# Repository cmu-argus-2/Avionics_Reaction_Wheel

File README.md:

Equipment:
- DC Power Supply (set to 12V, 0.9A) 
- Nucleo-G474RE mircocontroller board
- MCF8315C motor driver (on MCF8315EVM board, use VBAT not VM)
- 2804 Three Phase Brushless Motor / AS5600 FOC Encoder (DFRobot, SKU: FIT1034)

Arduino IDE Setup:
- Need STM32 MCU based boards by STMircoelectronics board manager installed
- Select Tools > Board part number: > Nucleo G474RE
- Select Nucleo-64 from board & port menu

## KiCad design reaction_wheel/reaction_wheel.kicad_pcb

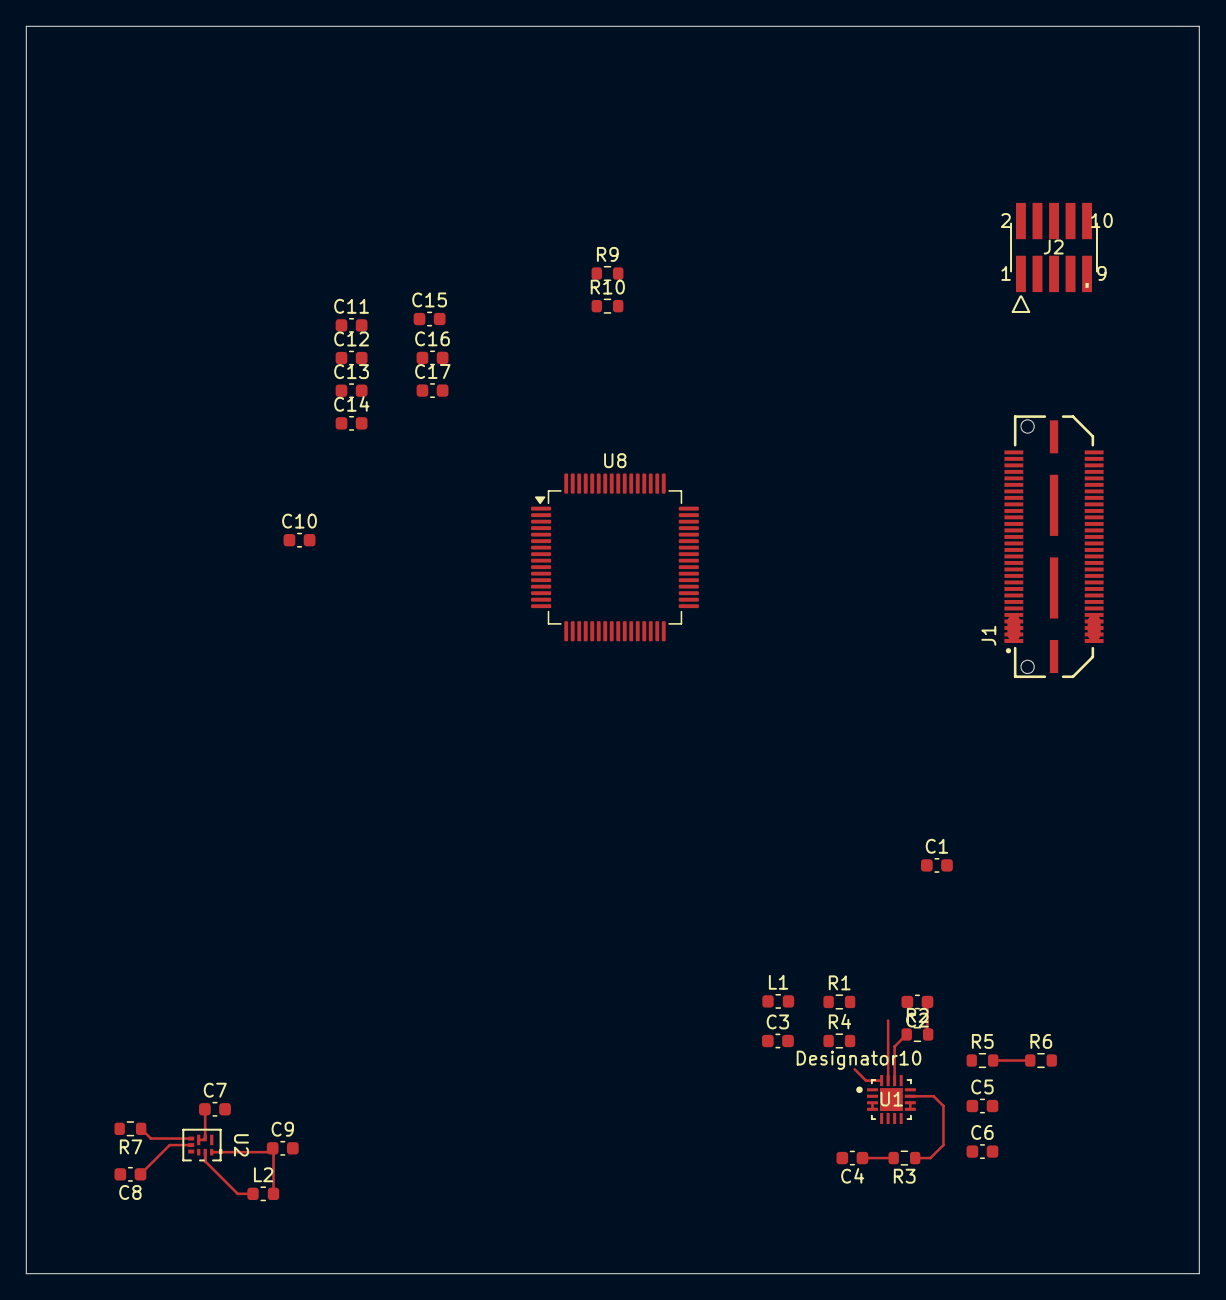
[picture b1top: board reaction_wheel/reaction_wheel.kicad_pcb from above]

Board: 2 copper layers, 90.2 x 95.9 mm, 33 parts (0 on the bottom side), 32 nets.

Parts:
C1, C6, C9: 22uF; C_0603_1608Metric
C2: 4.7nF; C_0603_1608Metric
C3: 0.1uF; C_0603_1608Metric
C4: 2.2uF; C_0603_1608Metric
C5: 1uF; C_0603_1608Metric
C7: 10uF; C_0603_1608Metric
C8: 10nF; C_0603_1608Metric
C10, C11, C12, C13, C14, C15, C16, C17: 100nF; C_0603_1608Metric
J1: QTH-030-01-L-D-A; SAMTEC-QTH-030-01-X-D-A
J2: FTSH-105-01-L-DV; CON10_2X5_DU_FTSH_SAI
L1, L2: 1uH; L_0603_1608Metric
R1, R3: 100k; R_0603_1608Metric
R2: 10k; R_0603_1608Metric
R4: 18k; R_0603_1608Metric
R5: 280k; R_0603_1608Metric
R6: 20k; R_0603_1608Metric
R7: 26.1k; R_0603_1608Metric
R9, R10: 4.7k; R_0603_1608Metric
U1: TPS61379QWRTERQ1; RTE0016K-IPC_B
U2: TPS62902RPJR; QFN_902RPJR_TEX
U8: STM32G474RETx; LQFP-64_10x10mm_P0.5mm

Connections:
+3V3: C9.1, C11.1, C12.1, C13.1, C14.1, C15.1, C16.1, C17.1, J2.1, L2.2, R9.1, R10.1, U2.3 (VOS), U8.1 (VBAT), U8.16 (VDD), U8.28 (VREF+), U8.29 (VDDA), U8.32 (VDD), U8.48 (VDD), U8.64 (VDD)
+3V3_P: J1.21, J1.22, J1.23, J1.24
/ADCS_EN: J1.38, U8.42 (PA8)
/NRST: C10.1, J2.10, U8.7 (PG10)
/Power/+12V: C5.1, C6.1, R5.1, U1.9 (VO), U1.10 (OUT)
/Power/BST_Boost: C3.2, U1.2 (BST)
/Power/COMP_Boost: R2.1, U1.14 (COMP)
/Power/EN_Boost: R1.2, U1.15 (EN)
/Power/FB_Boost: R5.2, R6.1, U1.13 (FB)
/Power/FREQ_Boost: R4.1, U1.16 (FREQ)
/Power/MODE_SCONF_Buck: R7.1, U2.7 (MODE/S-CONF)
/Power/PG_Boost: R3.1, U1.11 (PG)
/Power/SS_TR_Buck: C8.1, U2.8 (SS/TR)
/Power/SW_Boost: C3.1, L1.2, U1.3 (SW), U1.4 (SW)
/Power/SW_Buck: L2.1, U2.2 (SW)
/Power/VCC_Boost: C4.1, R3.2, U1.6 (VCC)
/RW_EN: J1.47, U8.17 (PA3)
/RW_MTR_ALRM: J1.53, U8.14 (PA2)
/RW_MTR_FLT: J1.51, U8.12 (PA0)
/RW_PWR_FLT: J1.49, U8.13 (PA1)
/RW_SCL: J1.55, R9.2, U8.59 (PB6)
/RW_SDA: J1.57, R10.2, U8.60 (PB7)
/SPIO_CLK: J1.29, U8.19 (PA5)
/SPIO_MISO: J1.33, U8.20 (PA6)
/SPIO_MOSI: J1.31, U8.21 (PA7)
/SPIO_NSS: J1.36, U8.18 (PA4)
/SWDCLK: J2.4, U8.50 (PA14)
/SWDIO: J2.2, U8.49 (PA13)
/SWO: J2.6, U8.56 (PB3)
GND: C1.2, C2.2, C4.2, C5.2, C6.2, C7.2, C8.2, C9.2, C10.2, C11.2, C12.2, C13.2, C14.2, C15.2, C16.2, C17.2, J1.11, J1.12, J1.13, J1.14, J1.15, J1.16, J1.17, J1.18, J1.19, J1.20, J1.25, J1.26, J1.27, J1.28, J1.35, J1.41, J1.44, J1.45, J1.59, J1.60, J2.3, J2.5, J2.9, R4.2, R6.2, R7.2, U1.5 (MODE_SYNC), U1.7 (GND), U1.8 (GND), U1.17 (Thermal_Pad), U2.4 (GND), U8.15 (VSS), U8.27 (VSSA), U8.31 (VSS), U8.47 (VSS), U8.63 (VSS)
unnamed: C2.1, R2.2
VBATT: C1.1, C7.1, J1.01 (Pin_1), J1.02 (Pin_2), J1.03 (Pin_3), J1.04 (Pin_4), J1.05 (Pin_5), J1.06 (Pin_6), J1.07 (Pin_7), J1.08 (Pin_8), J1.09 (Pin_9), J1.10, L1.1, R1.1, U1.1 (VIN), U2.5 (EN), U2.6 (VIN)

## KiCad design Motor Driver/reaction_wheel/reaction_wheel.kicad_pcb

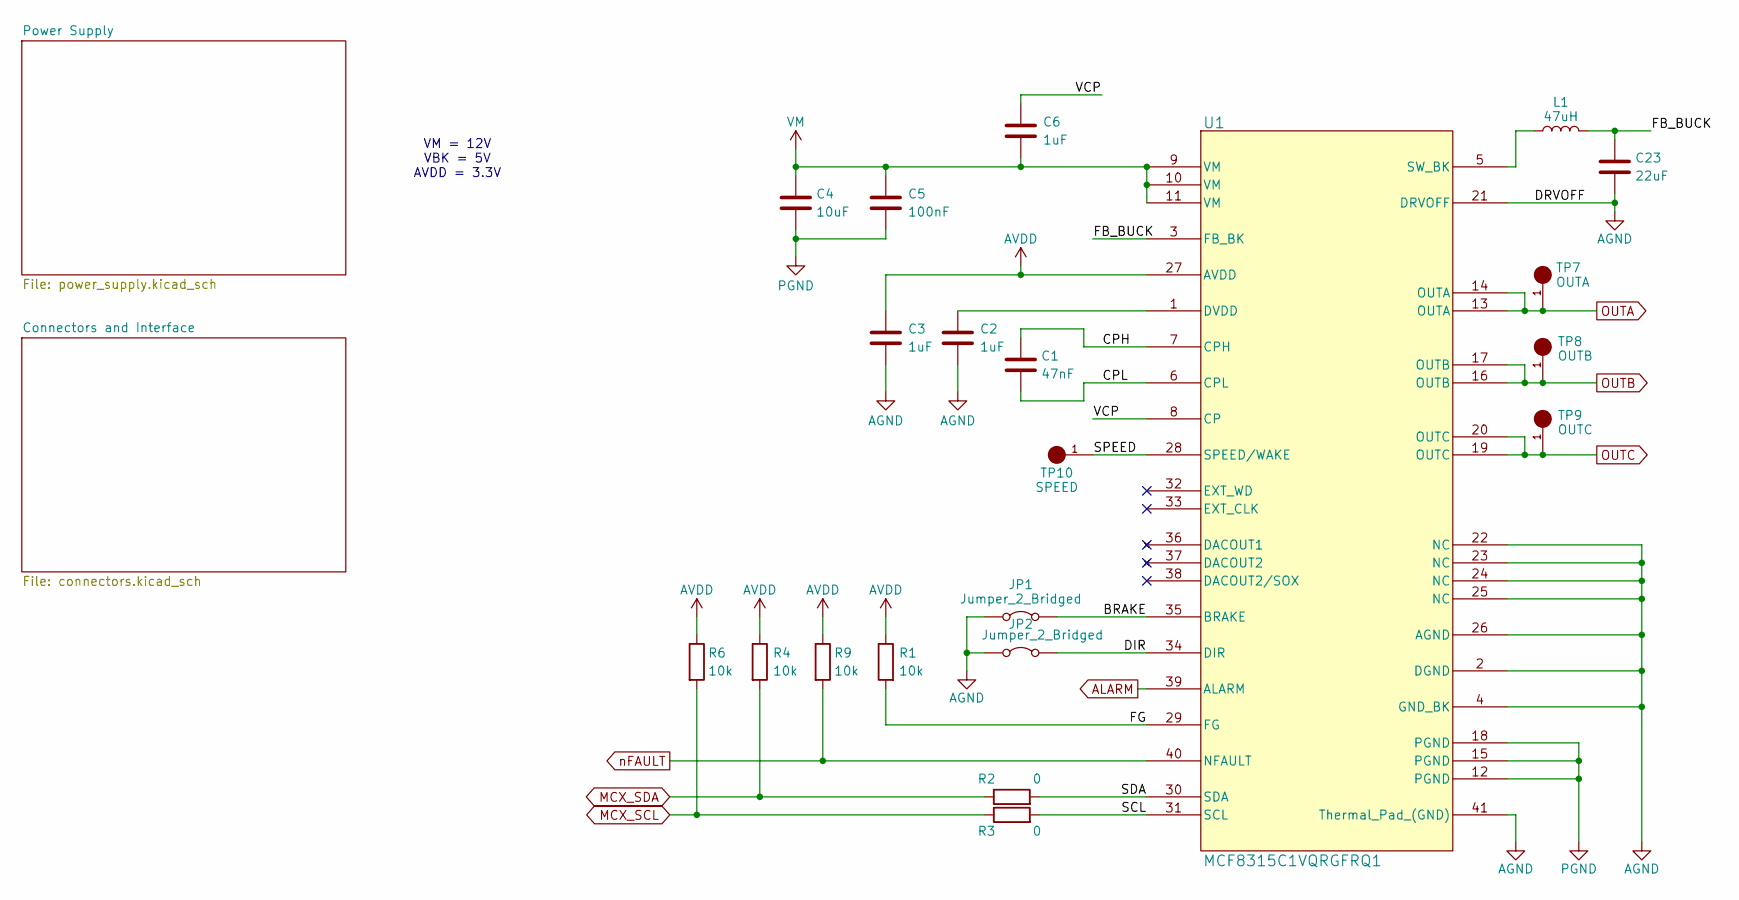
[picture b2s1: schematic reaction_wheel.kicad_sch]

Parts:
C1: 47nF; C_0603_1608Metric
C2, C3, C6: 1uF; C_0603_1608Metric
C4: 10uF; C_0805_2012Metric
C5: 100nF; C_0603_1608Metric
C23: 22uF; C_0603_1608Metric
JP1, JP2: Jumper_2_Bridged; SolderJumper-2_P1.3mm_Bridged_RoundedPad1.0x1.5mm
L1: 47uH; L_0603_1608Metric
R1, R4, R6, R9: 10k; R_0603_1608Metric
R2, R3: 0; R_0603_1608Metric
TP7: OUTA; TestPoint_Keystone_5000-5004_Miniature; MPN 5001; Digikey PN 36-5001-ND
TP8: OUTB; TestPoint_Keystone_5000-5004_Miniature; MPN 5001; Digikey PN 36-5001-ND
TP9: OUTC; TestPoint_Keystone_5000-5004_Miniature; MPN 5001; Digikey PN 36-5001-ND
TP10: SPEED; TestPoint_Keystone_5000-5004_Miniature; MPN 5001; Digikey PN 36-5001-ND
U1: MCF8315C1VQRGFRQ1; MCF8315C; MPN MCF8315C1VQRGFRQ1; Digikey PN 296-MCF8315C1VQRGFRQ1CT-ND

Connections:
/BRAKE: JP1.2 (B), U1.35 (BRAKE)
/CPH: C1.1, U1.7 (CPH)
/CPL: C1.2, U1.6 (CPL)
/DIR: JP2.2 (B), U1.34 (DIR)
/FB_BUCK: C23.1, L1.2, U1.3 (FB_BK)
/FG: R1.2, U1.29 (FG)
/SCL: R3.2, U1.31 (SCL)
/SDA: R2.2, U1.30 (SDA)
/SPEED: TP10.1, U1.28 (SPEED/WAKE)
/VCP: C6.1, U1.8 (CP)
AGND: C2.2, C3.2, C23.2, JP1.1 (A), JP2.1 (A), U1.2 (DGND), U1.4 (GND_BK), U1.21 (DRVOFF), U1.22 (NC), U1.23 (NC), U1.24 (NC), U1.25 (NC), U1.26 (AGND), U1.41 (Thermal_Pad_(GND)); also elsewhere on the board
ALARM: U1.39 (ALARM); also elsewhere on the board
AVDD: C3.1, R1.1, R4.1, R6.1, R9.1, U1.27 (AVDD)
MCX_SCL: R3.1, R6.2; also elsewhere on the board
MCX_SDA: R2.1, R4.2; also elsewhere on the board
unnamed: C2.1, U1.1 (DVDD)
unnamed: L1.1, U1.5 (SW_BK)
OUTA: TP7.1, U1.13 (OUTA), U1.14 (OUTA); also elsewhere on the board
OUTB: TP8.1, U1.16 (OUTB), U1.17 (OUTB); also elsewhere on the board
OUTC: TP9.1, U1.19 (OUTC), U1.20 (OUTC); also elsewhere on the board
PGND: C4.2, C5.2, U1.12 (PGND), U1.15 (PGND), U1.18 (PGND); also elsewhere on the board
VM: C4.1, C5.1, C6.2, U1.9 (VM), U1.10 (VM), U1.11 (VM); also elsewhere on the board
nFAULT: R9.2, U1.40 (NFAULT); also elsewhere on the board

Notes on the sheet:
VM = 12V VBK = 5V AVDD = 3.3V

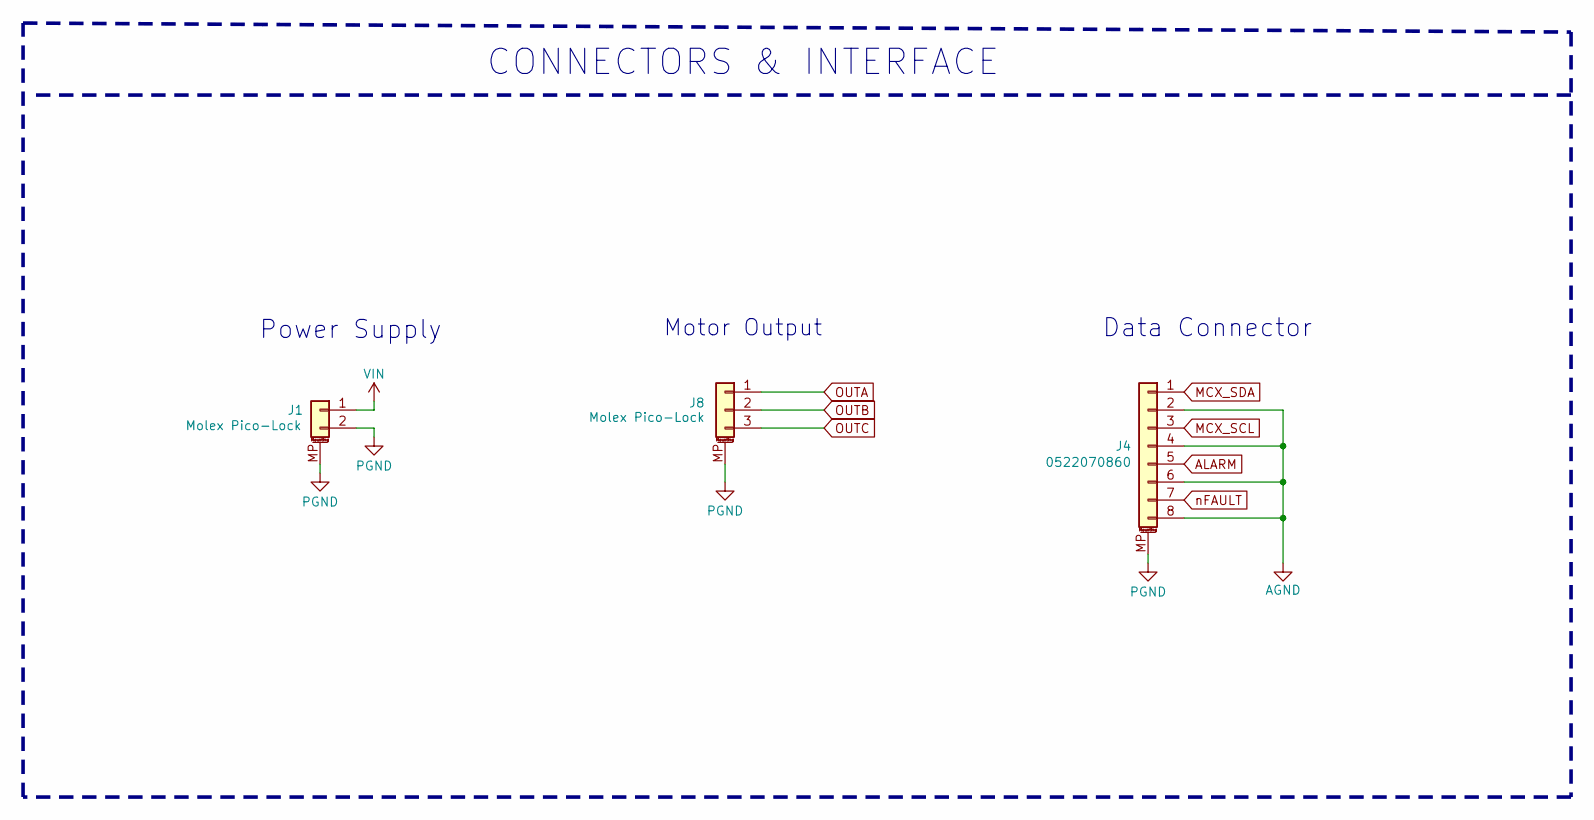
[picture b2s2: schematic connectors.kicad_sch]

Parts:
J1: Molex Pico-Lock; Molex_Pico-Lock_504050-0291_1x02-1MP_P1.50mm_Horizontal; Part Num 0781710002
J4: 0522070860; Molex 1x8 Right-Angle Conn; DigiKey PN 0522070860
J8: Molex Pico-Lock; Molex Pico-Lock 3 Socket Header; Part Number 0781710003

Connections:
AGND: J4.2, J4.4, J4.6, J4.8; also elsewhere on the board
ALARM: J4.5; also elsewhere on the board
MCX_SCL: J4.3; also elsewhere on the board
MCX_SDA: J4.1; also elsewhere on the board
OUTA: J8.1; also elsewhere on the board
OUTB: J8.2; also elsewhere on the board
OUTC: J8.3; also elsewhere on the board
PGND: J1.2, J1.MP (MountPin), J4.MP (MountPin), J8.MP (MountPin); also elsewhere on the board
VIN: J1.1; also elsewhere on the board
nFAULT: J4.7; also elsewhere on the board

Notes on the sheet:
CONNECTORS & INTERFACE
Data Connector
Motor Output
Power Supply

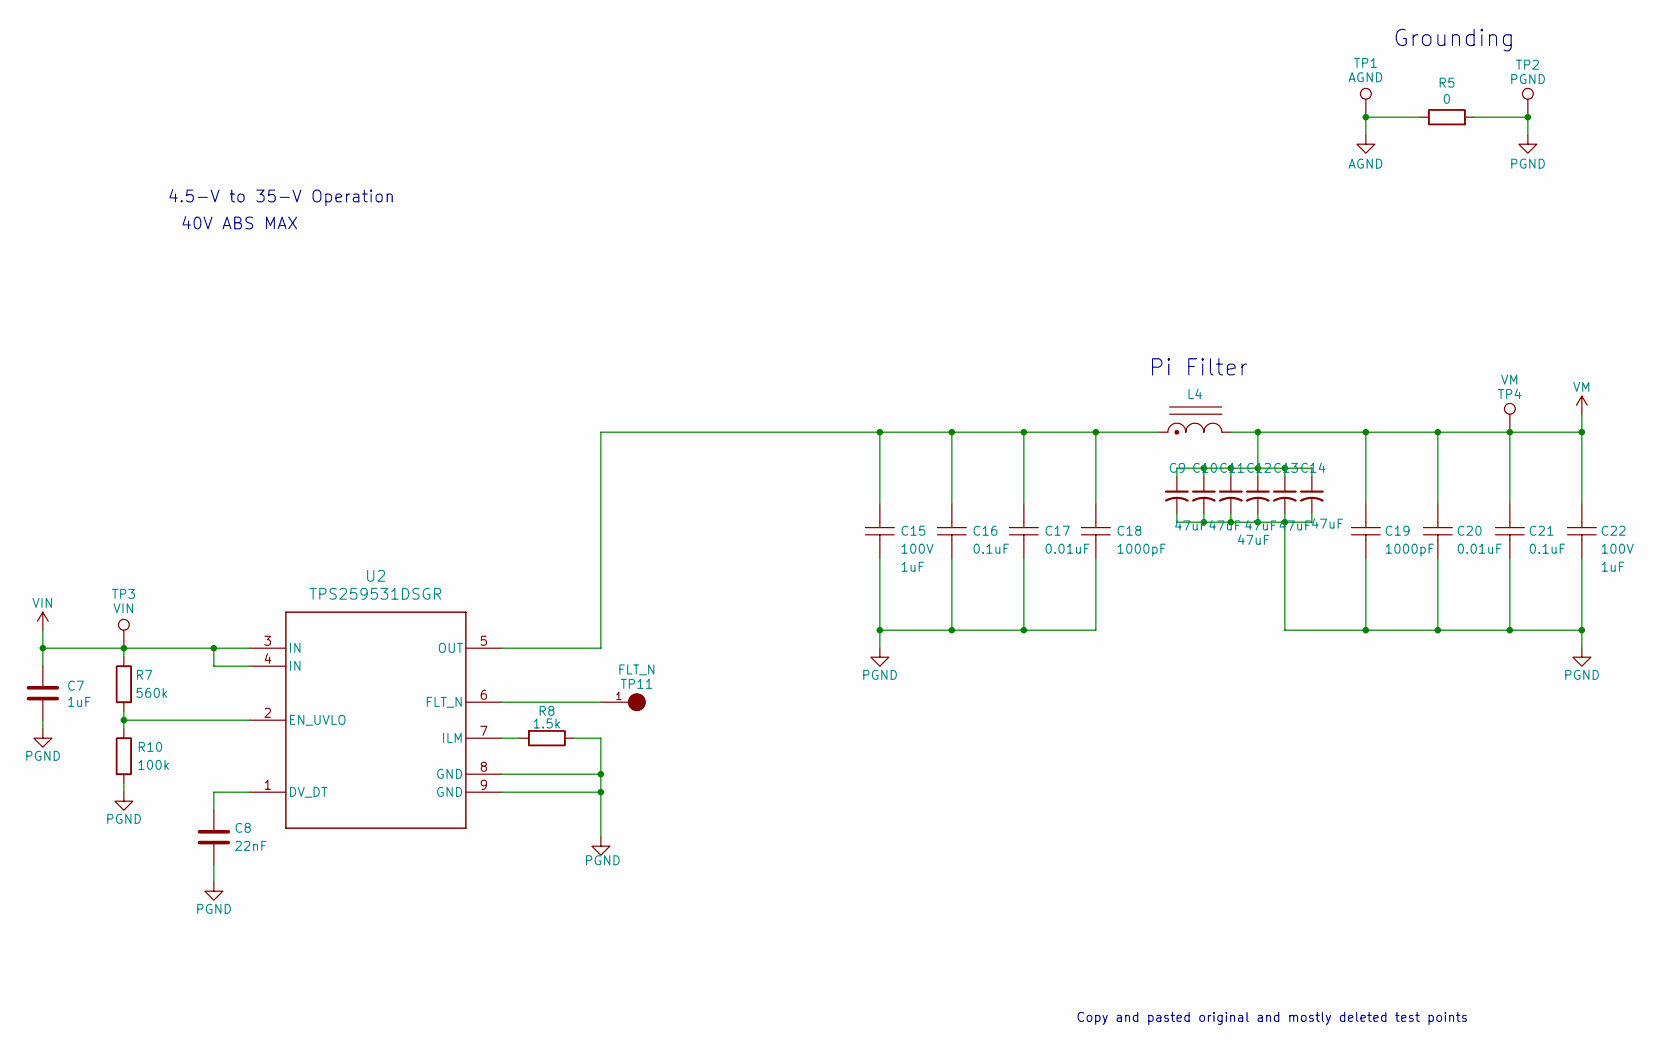
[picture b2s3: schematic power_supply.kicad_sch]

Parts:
C7: 1uF; C_0603_1608Metric
C8: 22nF; C_0603_1608Metric
C9, C10, C11, C12, C13, C14: 47uF; C_1206_3216Metric; DigiKey PN C3216X5R1E476M160AC
C15, C22: CGA3E3X7S2A104K080AB; C_0603_1608Metric; TOLERANCE_% 10%; PARTNUMBER CL31B105KCHNNNE
C16, C21: CGA3E3X7S2A104K080AB; C_0603_1608Metric; TOLERANCE_% 10%; PARTNUMBER CGA3E3X7S2A104K080AB
C17, C20: CGA3E2X7R2A103K080AA; C_0603_1608Metric; TOLERANCE_% 10%; PARTNUMBER CGA3E2X7R2A103K080AA
C18, C19: CGA3E2X7R2A102K080AA; C_0603_1608Metric; TOLERANCE_% 10%; PARTNUMBER CGA3E2X7R2A102K080AA
L4: XAL5030-102MEC; L_Coilcraft_XAL5030-XXX
R5: 0; R_0603_1608Metric
R7: 560k; R_0603_1608Metric
R8: 1.5k; R_0603_1608Metric
R10: 100k; R_0603_1608Metric
TP1: AGND; TestPoint_Keystone_5000-5004_Miniature
TP2: PGND; TestPoint_Keystone_5000-5004_Miniature
TP3: VIN; TestPoint_Keystone_5000-5004_Miniature
TP4: VM; TestPoint_Keystone_5000-5004_Miniature
TP11: FLT_N; TestPoint_Keystone_5000-5004_Miniature; MPN 5001; Digikey PN 36-5001-ND
U2: TPS259531DSGR; eFuse TPS259531DSGR_NV; Part Number TPS259531DSGR

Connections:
AGND: R5.1, TP1.1 (1_1); also elsewhere on the board
unnamed: C8.1, U2.1 (DV_DT)
unnamed: R7.2, R10.1, U2.2 (EN_UVLO)
unnamed: TP11.1, U2.6 (FLT_N)
unnamed: R8.2, U2.7 (ILM)
unnamed: C15.1, C16.1, C17.1, C18.1, L4.1, U2.5 (OUT)
PGND: C7.2, C8.2, C9.2, C10.2, C11.2, C12.2, C13.2, C14.2, C15.2, C16.2, C17.2, C18.2, C19.2, C20.2, C21.2, C22.2, R5.2, R8.1, R10.2, TP2.1 (1_1), U2.8 (GND), U2.9 (GND); also elsewhere on the board
VIN: C7.1, R7.1, TP3.1 (1_1), U2.3 (IN), U2.4 (IN); also elsewhere on the board
VM: C9.1, C10.1, C11.1, C12.1, C13.1, C14.1, C19.1, C20.1, C21.1, C22.1, L4.2, TP4.1 (1_1); also elsewhere on the board

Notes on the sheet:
40V ABS MAX
Grounding
Copy and pasted original and mostly deleted test points
Pi Filter
4.5-V to 35-V Operation

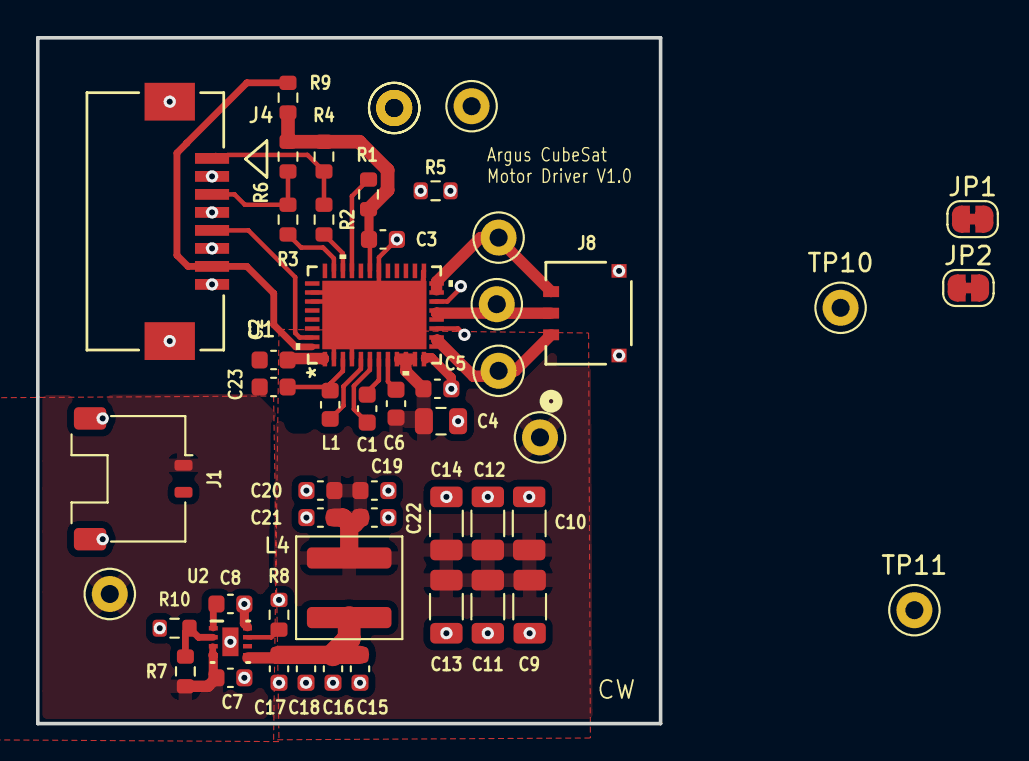
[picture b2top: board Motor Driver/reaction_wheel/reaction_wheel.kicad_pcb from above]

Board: 2 copper layers, 34.6 x 38.1 mm, 52 parts (0 on the bottom side), 29 nets.

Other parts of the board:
TP1#2: AGND; TestPoint_Keystone_5000-5004_Miniature

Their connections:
AGND: TP1#2.1 (1_1); also elsewhere on the board

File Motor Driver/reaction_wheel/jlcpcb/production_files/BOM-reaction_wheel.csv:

Comment,Designator,Footprint,LCSC,Quantity
0,"R2,R3,R5",R_0603_1608Metric,C1952,3
100k,R10,R_0603_1608Metric,C15458,1
100nF,C5,C_0603_1608Metric,C1591,1
10k,"R4,R6",R_0603_1608Metric,C15401,2
10uF,C4,C_0805_2012Metric,C15850,1
1500,R8,R_0603_1608Metric,C22843,1
1uF,"C2,C3,C6,C7",C_0603_1608Metric,C15849,4
22nF,C8,C_0603_1608Metric,C21122,1
22uF,C23,C_0603_1608Metric,C86295,1
47nF,C1,C_0603_1608Metric,C1622,1
47uH,L1,L_0603_1608Metric,C3910945,1
5.1k,"R1,R9",R_0603_1608Metric,C23186,2
560k,R7,R_0603_1608Metric,C23203,1
CGA3E2X7R2A102K080AA,"C18,C19",C_0603_1608Metric,C1588,2
CGA3E2X7R2A103K080AA,"C17,C20",C_0603_1608Metric,C1589,2
CGA3E3X7S2A104K080AB,"C15,C22",C_0603_1608Metric,C15849,2
CGA3E3X7S2A104K080AB,"C16,C21",C_0603_1608Metric,C1591,2
Data Conn,J4,Molex 1x8 Right-Angle Conn,C587867,1
Input Power,J1,Molex_Pico-Lock_504050-0291_1x02-1MP_P1.50mm_Horizontal,C5119943,1
MCF8315C1VQRGFRQ1,U1,MCF8315C,C31301704,1
MOTOR_OUT,J8,Molex Pico-Lock 3 Socket Header,C564183,1
TPS259531DSGR,U2,eFuse TPS259531DSGR_NV,C2155674,1
XAL5030-102MEC,L4,L_Coilcraft_XAL5030-XXX,C5379798,1

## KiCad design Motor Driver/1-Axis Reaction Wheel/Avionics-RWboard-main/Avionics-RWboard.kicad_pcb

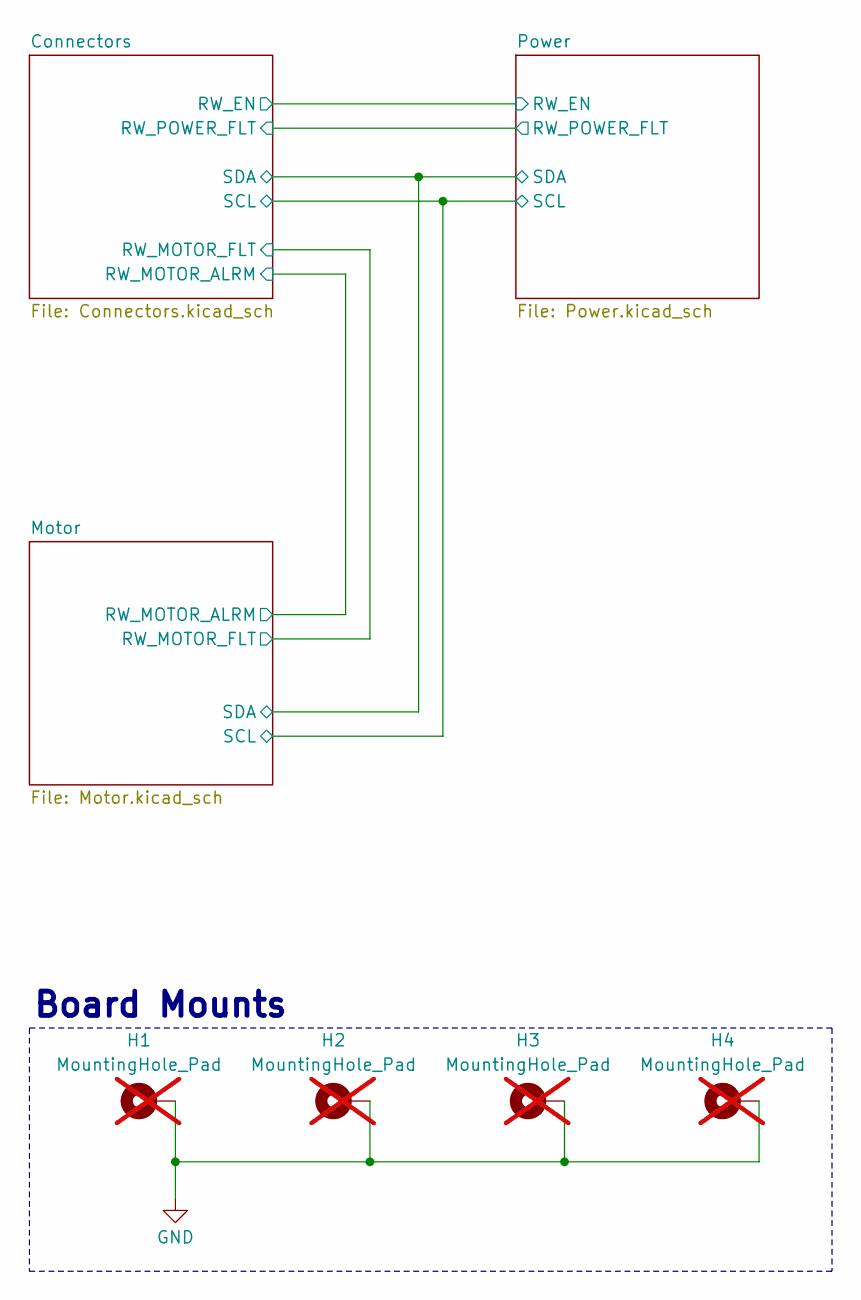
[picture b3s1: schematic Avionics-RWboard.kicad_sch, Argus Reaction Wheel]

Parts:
H1, H2, H3, H4: MountingHole_Pad; MountingHole_3.2mm_M3_Pad_Via; not fitted

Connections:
GND: H1.1 (1_1), H2.1 (1_1), H3.1 (1_1), H4.1 (1_1); also elsewhere on the board

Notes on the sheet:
Board Mounts

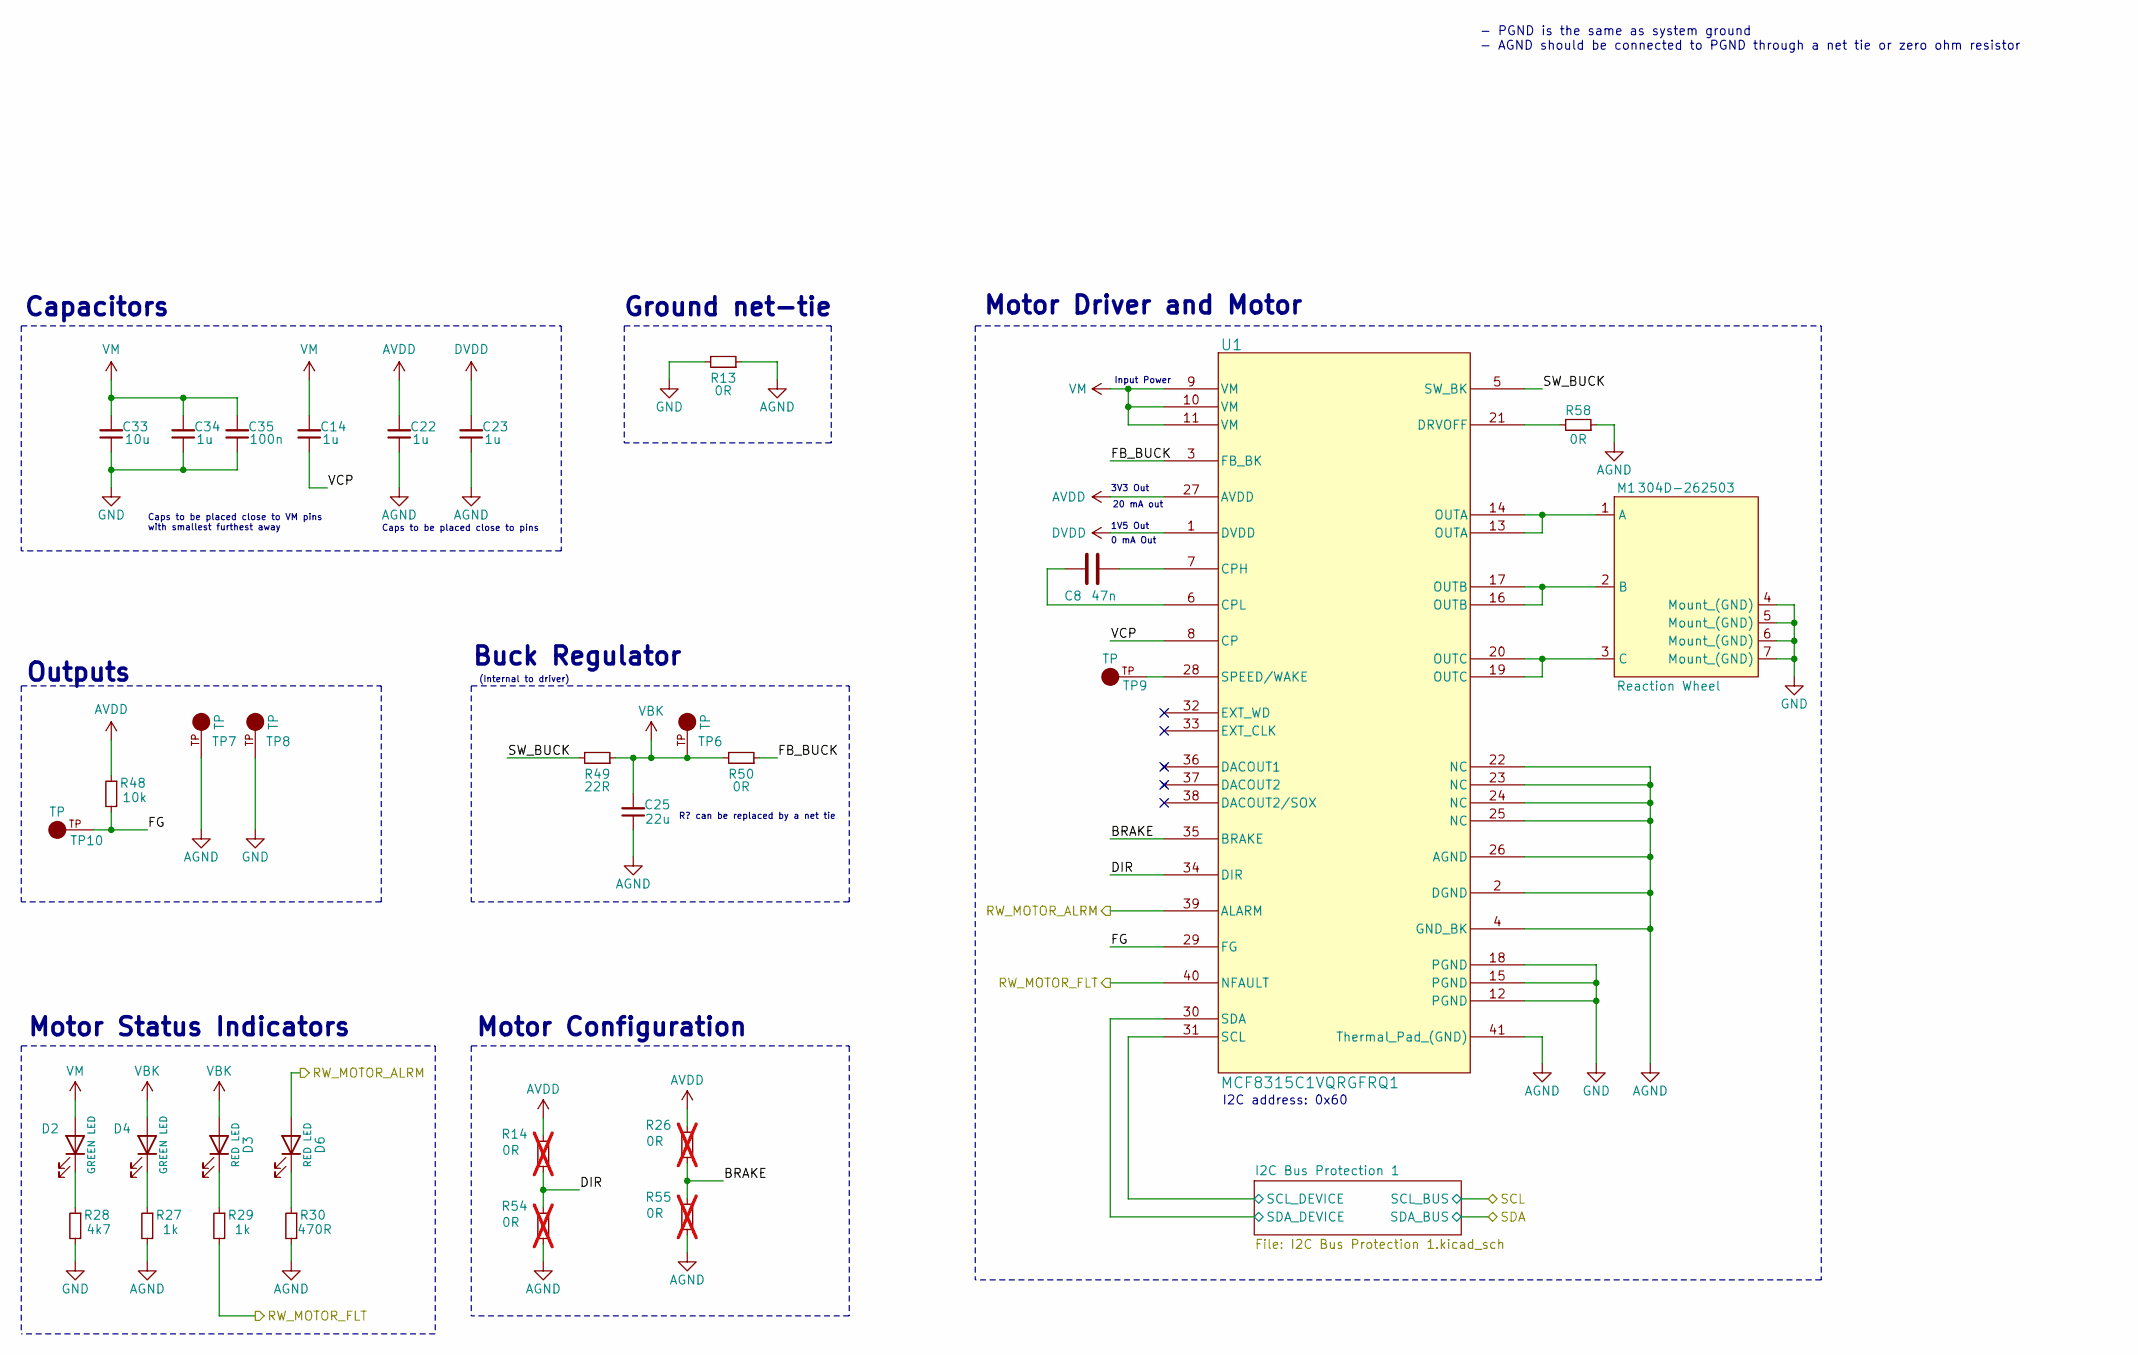
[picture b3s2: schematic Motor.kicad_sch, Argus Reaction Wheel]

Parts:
C8: 47n; C_0603_1608Metric; Part GCM188R71H473KA55D; Digikey PN 490-4934-1-ND
C14, C22, C23, C34: 1u; C_0603_1608Metric; Part CL10B105KA8NNNC; Digikey PN 1276-1184-1-ND
C25: 22u; C_0603_1608Metric; MPN CL10A226MP8NUNE; Digikey PN 1276-1274-1-ND
C33: 10u; C_1206_3216Metric_Pad1.33x1.80mm_HandSolder; Part CL31B106KAHNNNE; Digikey PN 1276-1804-1-ND
C35: 100n; C_0402_1005Metric_Pad0.74x0.62mm_HandSolder; Part C0402C103K3RACTU; Digikey PN 399-C0402C103K3RACTUCT-ND
D2, D4: GREEN LED; LED_0603_1608Metric; Manufacturer_Part_Number LTST-C190KGKT; Digikey PN 1830-1064-1-ND
D3, D6: RED LED; LED_0603_1608Metric; Manufacturer_Part_Number LTST-C190KRKT; Digikey PN 1830-1065-1-ND
M1: 304D-262503; Reaction_Wheel; MPN 304D-262503; Digikey PN 4827-304D-262503CT-ND
R13, R50: 0R; R_0805_2012Metric_Pad1.20x1.40mm_HandSolder; MPN RC0805JR-070RL; Digikey PN 311-0.0ARCT-ND
R14, R26, R54, R55: 0R; R_0402_1005Metric_Pad0.72x0.64mm_HandSolder; MPN RC0402JR-070RL; Digikey PN 311-0.0JRCT-ND; not fitted
R27, R29: 1k; R_0603_1608Metric; MPN RC0603FR-071KL; Digikey PN 311-1.00KHRCT-ND
R28: 4k7; R_0603_1608Metric; MPN RC0603FR-074K7L; Digikey PN 311-4.70KHRCT-ND
R30: 470R; R_0603_1608Metric; MPN RC0603FR-13470RL; Digikey PN 13-RC0603FR-13470RLCT-ND
R48: 10k; R_0603_1608Metric; MPN RC0603FR-0710KL; Digikey PN 311-10.0KHRCT-ND
R49: 22R; R_2512_6332Metric_Pad1.40x3.35mm_HandSolder; Part CRCW251222R0FKEGHP; Digikey PN 541-CRCW251222R0FKEGHPCT-ND
R58: 0R; R_0402_1005Metric_Pad0.72x0.64mm_HandSolder; MPN RC0402JR-070RL; Digikey PN 311-0.0JRCT-ND
TP6, TP7, TP8, TP9, TP10: TP; KEYSTONE_5001; MPN 5001; Digikey PN 36-5001-ND
U1: MCF8315C1VQRGFRQ1; VQFN40_RGF_TEX; MPN MCF8315C1VQRGFRQ1; Digikey PN 296-MCF8315C1VQRGFRQ1CT-ND

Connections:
/Connectors/RW_MOTOR_ALRM: D6.2 (A), U1.39 (ALARM); also elsewhere on the board
/Connectors/RW_MOTOR_FLT: R29.2, U1.40 (NFAULT); also elsewhere on the board
/Motor/BRAKE: R26.1, R55.2, U1.35 (BRAKE)
/Motor/DIR: R14.1, R54.2, U1.34 (DIR)
/Motor/FB_BUCK: R50.1, U1.3 (FB_BK)
/Motor/FG: R48.2, TP10.TP, U1.29 (FG)
/Motor/I2C Bus Protection 1/SCL_DEVICE: U1.31 (SCL); also elsewhere on the board
/Motor/I2C Bus Protection 1/SDA_DEVICE: U1.30 (SDA); also elsewhere on the board
/Motor/SW_BUCK: R49.2, U1.5 (SW_BK)
/Motor/VCP: C14.1, U1.8 (CP)
AGND: C22.1, C23.1, C25.1, R13.1, R27.2, R30.2, R54.1, R55.1, R58.1, TP7.TP, U1.2 (DGND), U1.4 (GND_BK), U1.22 (NC), U1.23 (NC), U1.24 (NC), U1.25 (NC), U1.26 (AGND), U1.41 (Thermal_Pad_(GND))
AVDD: C22.2, R14.2, R26.2, R48.1, U1.27 (AVDD)
DVDD: C23.2, U1.1 (DVDD)
GND: C33.1, C34.1, C35.1, M1.4 (Mount_(GND)), M1.5 (Mount_(GND)), M1.6 (Mount_(GND)), M1.7 (Mount_(GND)), R13.2, R28.2, TP8.TP, U1.12 (PGND), U1.15 (PGND), U1.18 (PGND); also elsewhere on the board
unnamed: D2.1 (K), R28.1
unnamed: D3.1 (K), R29.1
unnamed: D4.1 (K), R27.1
unnamed: D6.1 (K), R30.1
unnamed: M1.1 (A), U1.13 (OUTA), U1.14 (OUTA)
unnamed: M1.2 (B), U1.16 (OUTB), U1.17 (OUTB)
unnamed: M1.3 (C), U1.19 (OUTC), U1.20 (OUTC)
unnamed: C8.1, U1.7 (CPH)
unnamed: C8.2, U1.6 (CPL)
unnamed: R58.2, U1.21 (DRVOFF)
unnamed: TP9.TP, U1.28 (SPEED/WAKE)
VBK: C25.2, D3.2 (A), D4.2 (A), R49.1, R50.2, TP6.TP
VM: C14.2, C33.2, C34.2, C35.2, D2.2 (A), U1.9 (VM), U1.10 (VM), U1.11 (VM); also elsewhere on the board

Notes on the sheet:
20 mA out
3V3 Out
Caps to be placed close to pins
Buck Regulator
0 mA Out
R? can be replaced by a net tie
Input Power
Motor Status Indicators
I2C address: 0x60
Motor Driver and Motor
Caps to be placed close to VM pins with smallest furthest away
Ground net-tie
Outputs
1V5 Out
- PGND is the same as system ground - AGND should be connected to PGND through a net tie or zero ohm resistor
Motor Configuration
(Internal to driver)
Capacitors

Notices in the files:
parts and their libraries:
License: Apache-2.0
